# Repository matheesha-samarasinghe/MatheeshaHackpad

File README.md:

# Matheesha's Hackpad Controller
Macropad used to control a robotic arm.

## Inspiration
I wanted to control a robotic arm I'm working on using buttons for manual testing, so I decided to make this hackpad.

## Design Overview

| Schematics | PCB | 3D Design |
|------------|-----|-----------|
|  |  |  |

## BOM (Bill of Materials)
- 9x Cherry MX Switches  
- 2x SK6812 MINI LEDs  
- 1x XIAO RP2040  
- 9x Blank DSA Keycaps  
- 4x M3x16 Bolts  
- 4x M3 Heatset Inserts

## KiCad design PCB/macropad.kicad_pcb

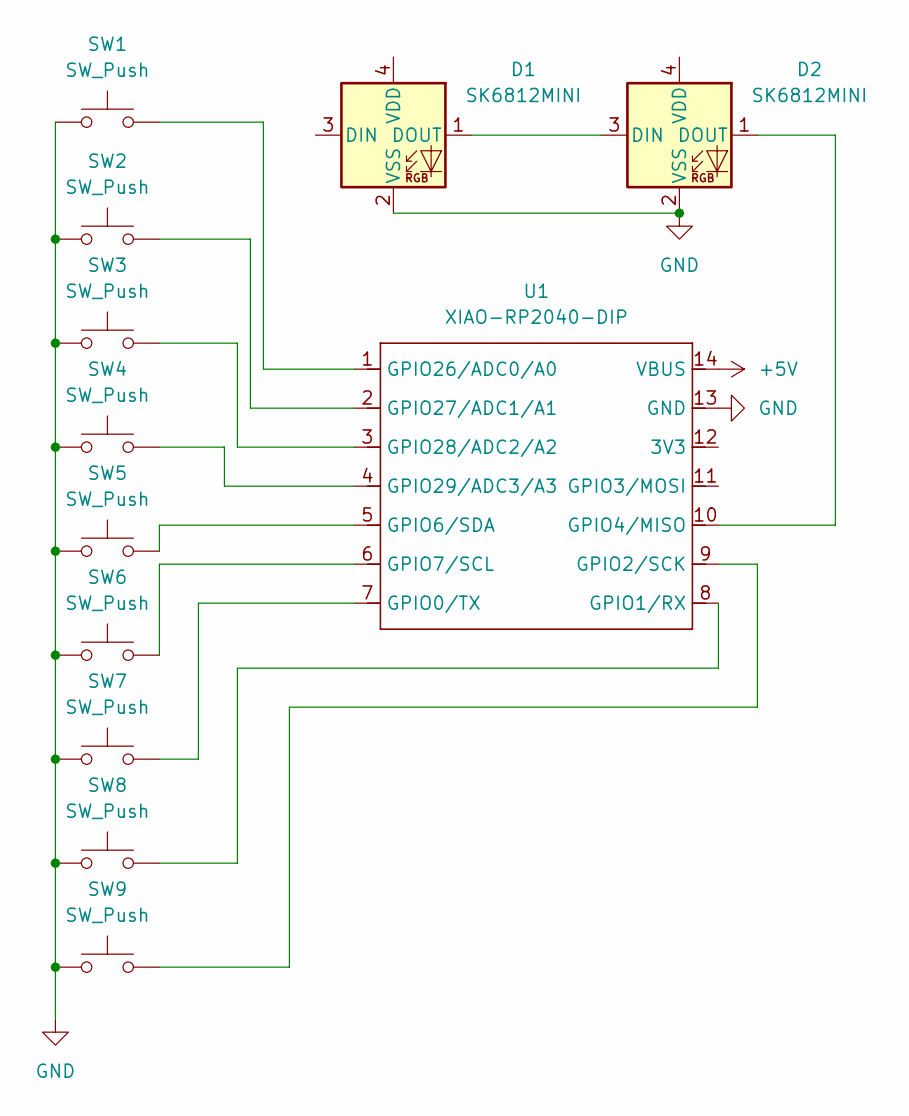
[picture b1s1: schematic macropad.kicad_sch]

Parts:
D1, D2: SK6812MINI; LED_SK6812MINI_PLCC4_3.5x3.5mm_P1.75mm
SW1, SW2, SW3, SW4, SW5, SW6, SW7, SW8, SW9: SW_Push; SW_Cherry_MX_1.00u_PCB
U1: XIAO-RP2040-DIP

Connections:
+5V: U1.14 (VBUS)
GND: D1.2 (VSS), D2.2 (VSS), SW1.1, SW2.1, SW3.1, SW4.1, SW5.1, SW6.1, SW7.1, SW8.1, SW9.1, U1.13 (GND)
unnamed: D1.1 (DOUT), D2.3 (DIN)
unnamed: D2.1 (DOUT), U1.10 (GPIO4/MISO)
unnamed: SW7.2, U1.7 (GPIO0/TX)
unnamed: SW8.2, U1.8 (GPIO1/RX)
unnamed: SW9.2, U1.9 (GPIO2/SCK)
unnamed: SW5.2, U1.5 (GPIO6/SDA)
unnamed: SW6.2, U1.6 (GPIO7/SCL)
unnamed: SW1.2, U1.1 (GPIO26/ADC0/A0)
unnamed: SW2.2, U1.2 (GPIO27/ADC1/A1)
unnamed: SW3.2, U1.3 (GPIO28/ADC2/A2)
unnamed: SW4.2, U1.4 (GPIO29/ADC3/A3)

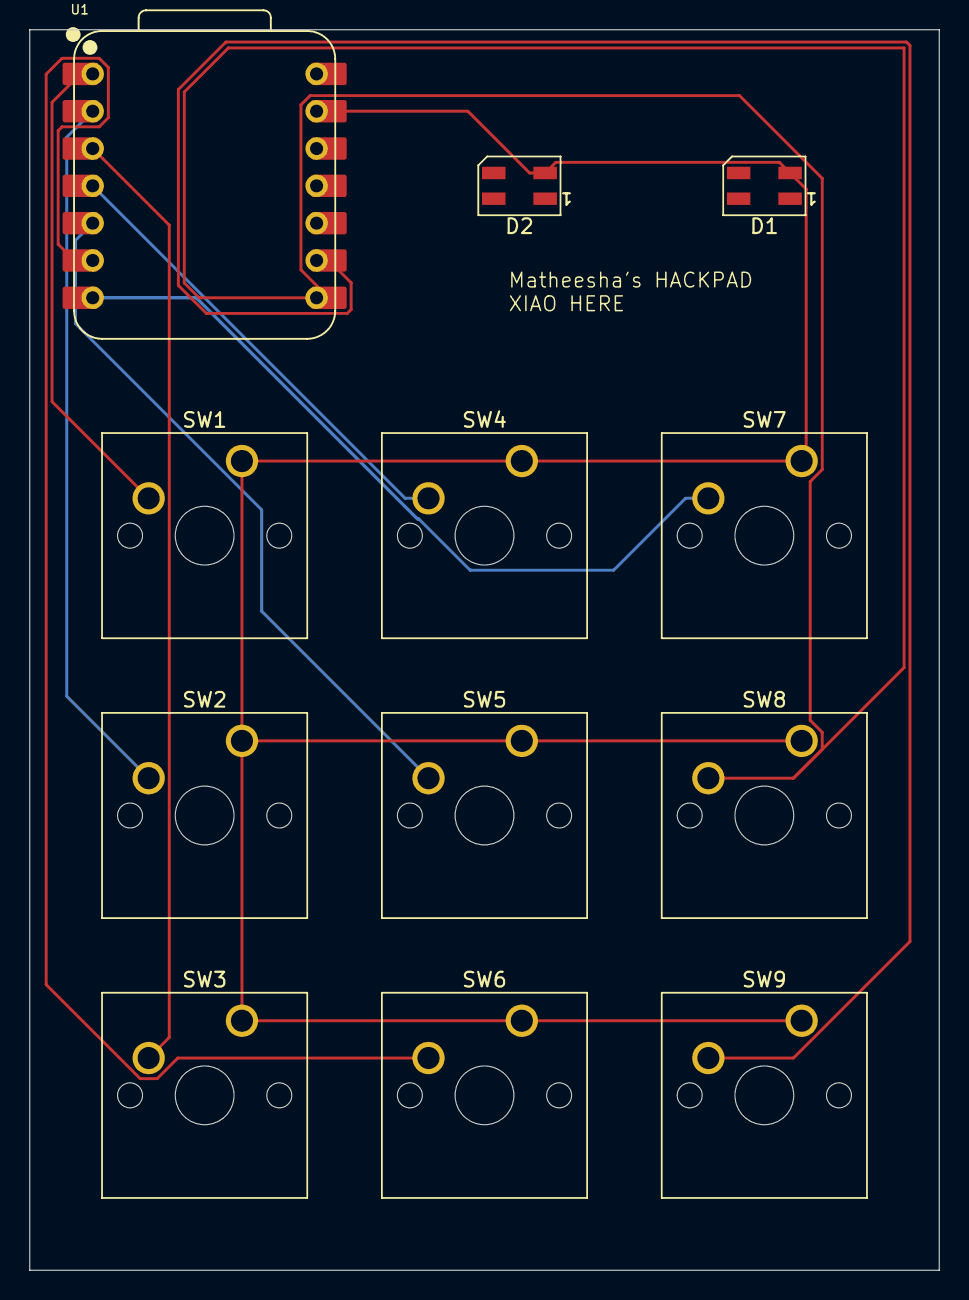
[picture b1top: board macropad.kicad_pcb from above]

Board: 2 copper layers, 61.9 x 84.4 mm, 12 parts (0 on the bottom side), 12 nets.
